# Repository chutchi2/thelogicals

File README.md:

# thelogicals
General file sharing for The Logicals in 2016-2017
This repostiory will contain presentations, Scripts and everything in between. 
Tiffany says its lame
Robert says its baffling

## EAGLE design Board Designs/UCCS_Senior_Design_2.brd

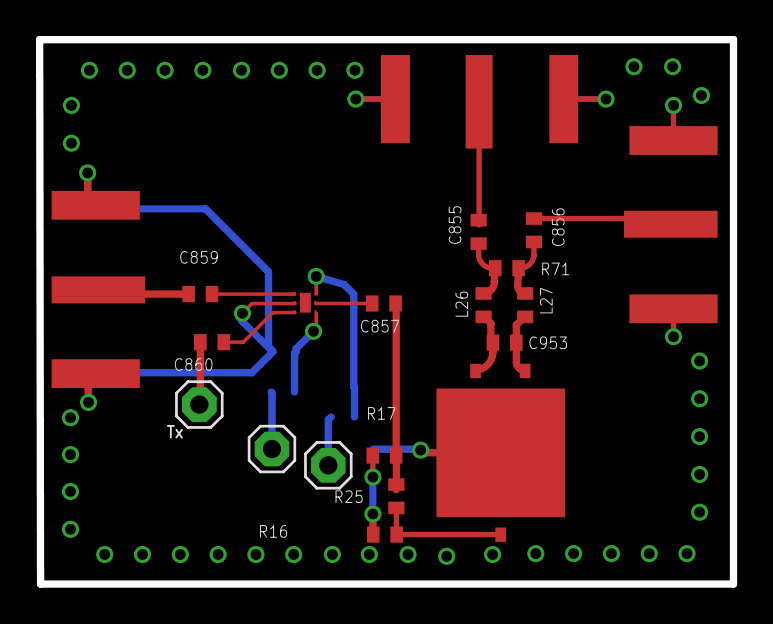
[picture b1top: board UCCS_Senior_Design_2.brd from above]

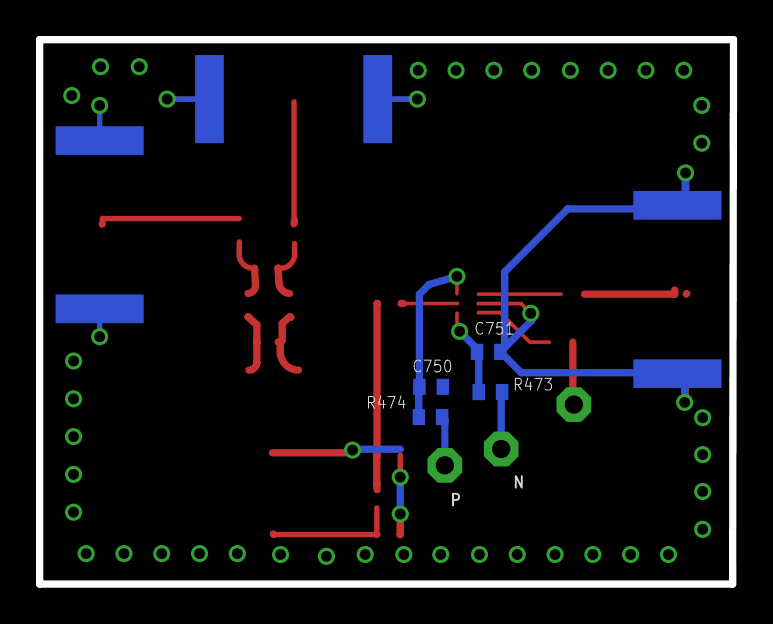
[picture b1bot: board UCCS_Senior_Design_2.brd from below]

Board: 2 copper layers, 38.5 x 30.2 mm, 24 parts (4 on the bottom side), 15 nets.

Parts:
C750, C751, C855, C856, C857, C859, C860: 100 pF; C0402
C953: 400 fF; C0402
E$2: SKY13431-374LF
E$3, E$4, E$5: SMA132289
E$6: BALH-0006SMG
L26, L27: 1 nH; R0402
R16, R17: 221 Ohm; R0402
R25: 23.7 Ohm; R0402
R71: 93.7 Ohm; R0402
R473, R474: 100 Ohm; R0402
RX1_N1, RX1_N2, RX1_P1: 1X01

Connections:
GND: C751.2, E$3.GND, E$3.P$5, E$4.GND, E$4.P$1, E$4.P$2, E$4.P$5, E$5.GND, E$5.P$1, E$5.P$2, E$5.P$5, E$6.GND, R16.2, R17.2
S$1: C751.1, R473.2
S$2: C750.1, R474.2
S$5: C855.2, E$5.P$3
S$6: R473.1, RX1_N1.1
S$10: R16.1, R25.2
S$24: C953.2, L26.1
S$32: C860.2, RX1_P1.1
S$37: R474.1, RX1_N2.1
S$38: C856.2, E$4.P$3
S$40: C953.1, L27.1
S$43: C855.1, L26.2, R71.1
S$44: C856.1, L27.2, R71.2
S$79: C859.2, E$3.P$3
S$85: C857.1, R17.1, R25.1

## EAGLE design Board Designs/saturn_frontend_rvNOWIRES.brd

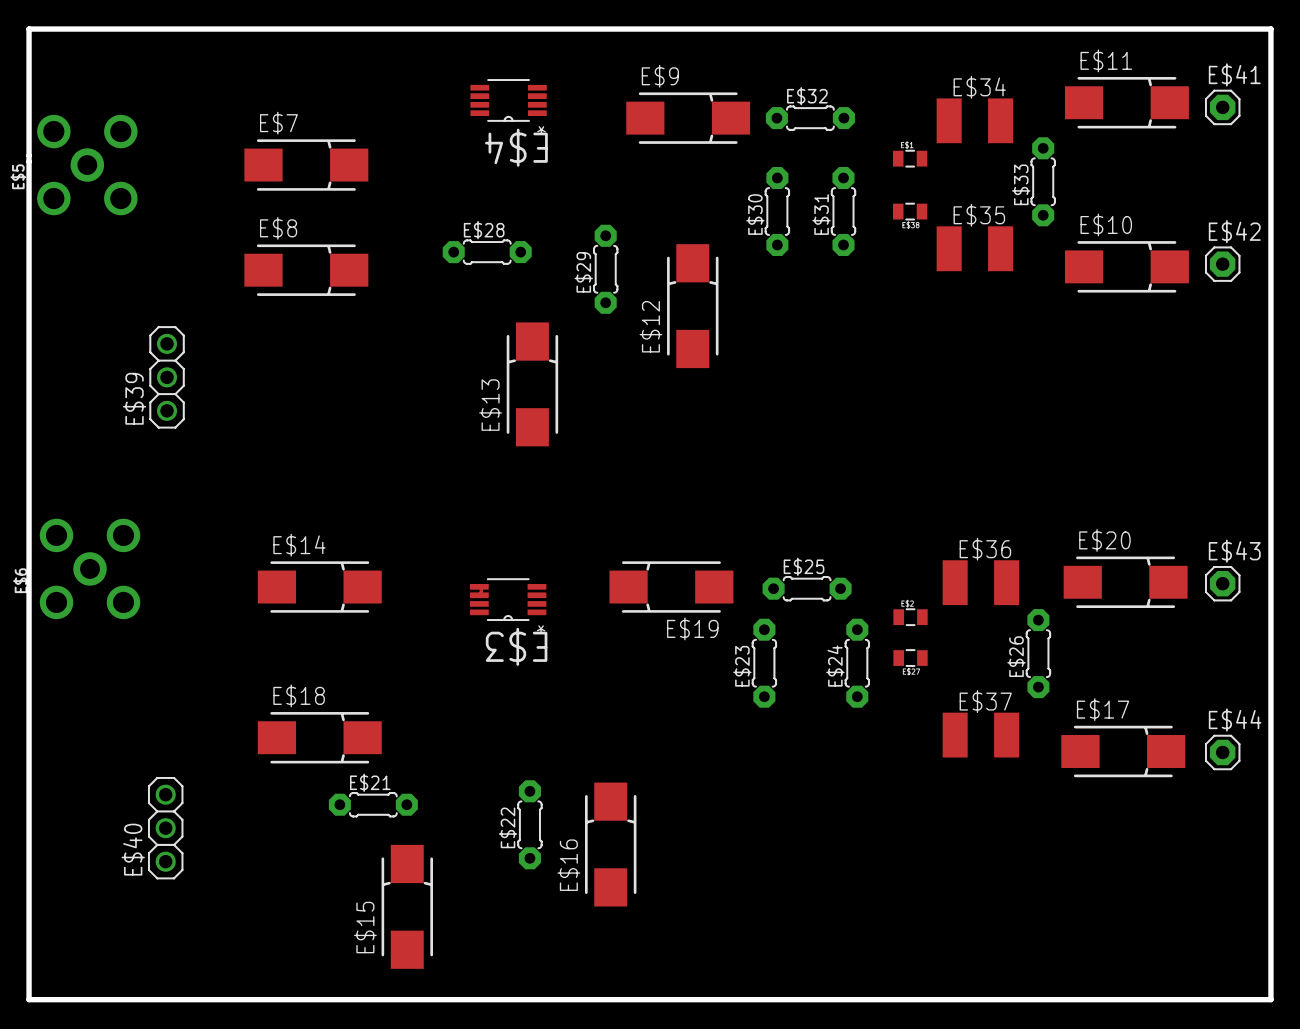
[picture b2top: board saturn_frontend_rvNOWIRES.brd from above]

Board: 2 copper layers, 94.2 x 73.6 mm, 44 parts (0 on the bottom side), 35 nets.

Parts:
E$1, E$2, E$27, E$38: 0805
E$3, E$4: SOP65P490X110-8N
E$5, E$6: SMA90_DIP
E$7, E$8, E$9, E$10, E$11, E$12, E$13, E$14, E$15, E$16, E$17, E$18, E$19, E$20: 100 pF; 085CS_1AR
E$21, E$22, E$28, E$29: 100 Ohm; 0204/5
E$23, E$24, E$30, E$31: 221 Ohm; 0204/5
E$25, E$32: 23.7 Ohm; 0204/5
E$26, E$33: 93.7 Ohm; 0204/5
E$34, E$35, E$36, E$37: 1.0 nH; L1812
E$39, E$40: 1X03
E$41, E$42, E$43, E$44: 1X01

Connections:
S$1: E$11.+, E$41.1
S$5: E$5.ANTENNA, E$7.-
S$6: E$10.-, E$33.1, E$35.2
S$7: E$8.-, E$39.3
S$8: E$28.1, E$39.2
S$10: E$2.1, E$24.2, E$25.2
S$11: E$10.+, E$42.1
S$12: E$11.-, E$33.2, E$34.2
S$14: E$2.2, E$36.1
S$16: E$4.5, E$7.+
S$17: E$20.+, E$43.1
S$18: E$4.8, E$8.+
S$21: E$17.+, E$44.1
S$22: E$4.1, E$28.2
S$23: E$4.2, E$29.2
S$25: E$29.1, E$39.1
S$26: E$9.+, E$30.2, E$32.1
S$27: E$1.1, E$31.2, E$32.2
S$28: E$1.2, E$34.1
S$29: E$35.1, E$38.1
S$32: E$18.-, E$40.3
S$33: E$21.1, E$40.2
S$34: E$22.1, E$40.1
S$36: E$6.ANTENNA, E$14.-
S$37: E$4.3, E$9.-
S$38: E$3.8, E$18.+
S$39: E$3.3, E$19.+
S$40: E$3.1, E$15.+, E$21.2
S$41: E$3.2, E$16.+, E$22.2
S$42: E$19.-, E$23.2, E$25.1
S$43: E$27.1, E$37.1
S$44: E$20.-, E$26.2, E$36.2
S$45: E$17.-, E$26.1, E$37.2
S$46: E$3.5, E$3.6, E$3.7, E$6.GND1, E$6.GND2, E$6.GND3, E$6.GND4, E$14.+, E$15.-, E$16.-, E$23.1, E$24.1, E$27.2
S$47: E$4.6, E$4.7, E$5.GND1, E$5.GND2, E$5.GND3, E$5.GND4, E$12.-, E$13.-, E$30.1, E$31.1, E$38.2

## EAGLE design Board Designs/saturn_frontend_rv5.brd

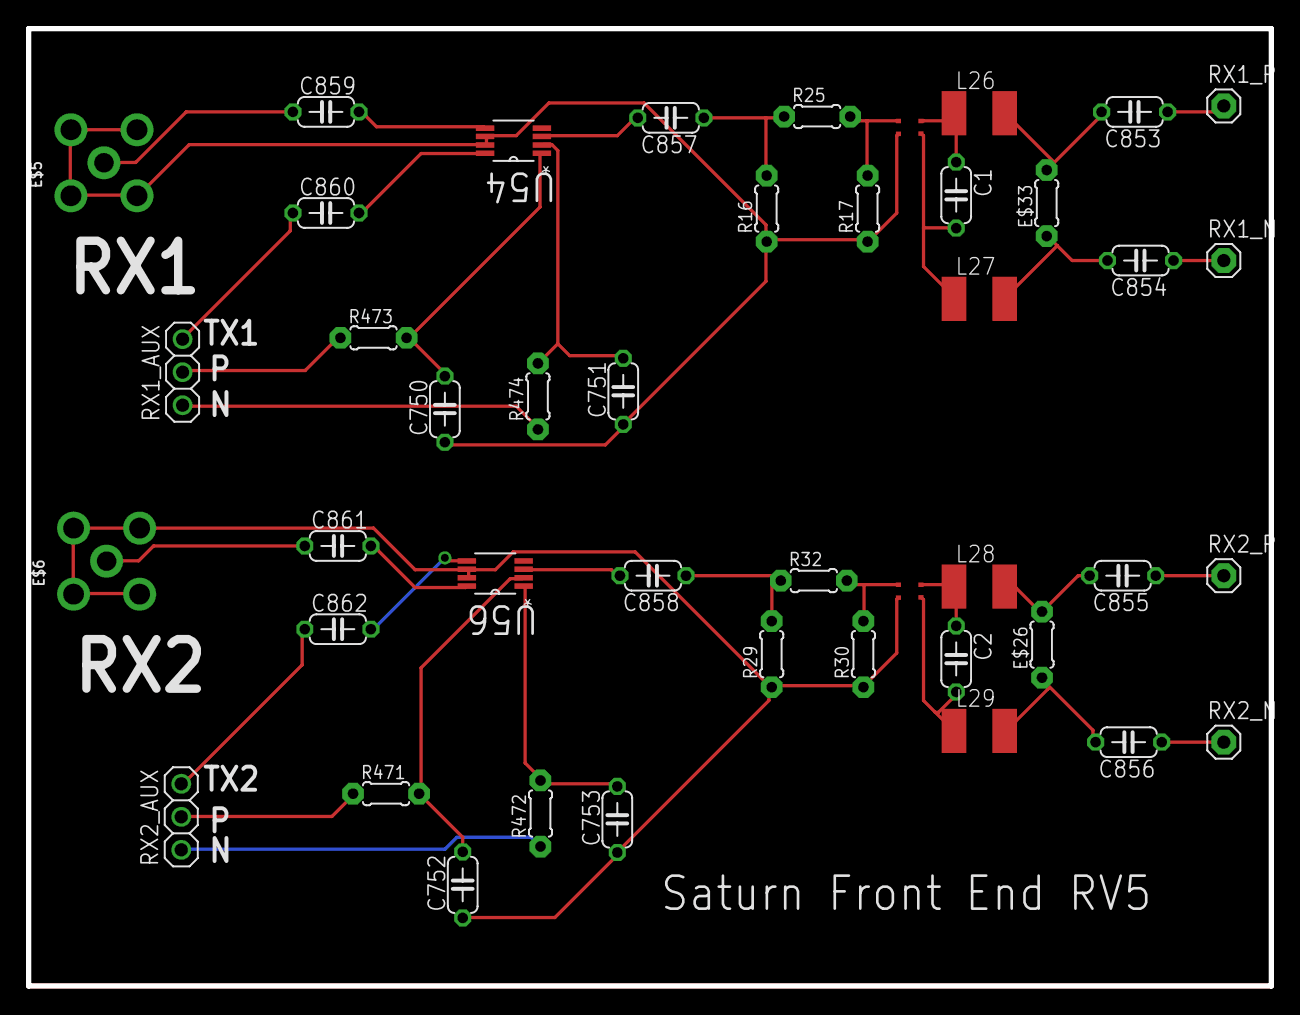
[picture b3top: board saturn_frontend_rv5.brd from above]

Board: 2 copper layers, 95.6 x 73.6 mm, 44 parts (0 on the bottom side), 36 nets.

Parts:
C1, C2: 400 fF; C050-024X044
C750, C751, C752, C753, C853, C854, C855, C856, C857, C858, C859, C860, C861: 100 pF; C050-024X044
C862: C050-024X044
E$1, E$2: BALUN_LOGICALS
E$5, E$6: SMA90_DIP
E$26, E$33: 93.7 Ohm; 0204/5
L26, L27, L28, L29: 1.0 nH; L1812
R16, R17, R29, R30: 221 Ohm; 0204/5
R25, R32: 23.7 Ohm; 0204/5
R471, R472, R473, R474: 100 Ohm; 0204/5
RX1_AUX, RX2_AUX: 1X03
RX1_N, RX1_P, RX2_N, RX2_P: 1X01
U54, U56: SOP65P490X110-8N

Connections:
S$1: E$2.1, R30.2, R32.2
S$2: C2.1, E$2.4, L28.1
S$3: C858.1, R29.2, R32.1
S$5: C855.2, E$26.2, L28.2
S$6: C855.1, RX2_P.1
S$7: C856.2, E$26.1, L29.2
S$8: C2.2, E$2.3, L29.1
S$10: C857.1, R16.2, R25.1
S$12: E$1.1, R17.2, R25.2
S$14: C1.1, E$1.4, L26.1
S$16: C1.2, E$1.3, L27.1
S$18: C853.2, E$33.2, L26.2
S$19: C854.2, E$33.1, L27.2
S$23: C853.1, RX1_P.1
S$24: C854.1, RX1_N.1
S$25: R473.1, RX1_AUX.2
S$27: C750.2, R473.2, U54.1
S$28: C751.2, R474.2, U54.2
S$29: R474.1, RX1_AUX.1
S$32: R471.1, RX2_AUX.2
S$33: C752.2, R471.2, U56.2
S$34: C753.2, R472.2, U56.1
S$35: C861.1, E$6.ANTENNA
S$36: C862.1, RX2_AUX.3
S$37: C860.1, RX1_AUX.3
S$38: C859.1, E$5.ANTENNA
S$39: C859.2, U54.5
S$40: C860.2, U54.8
S$41: C862.2, U56.5
S$42: C861.2, U56.8
S$43: C858.2, U56.3
S$44: C857.2, U54.3
S$45: C750.1, C751.1, E$1.2, E$5.GND1, E$5.GND2, E$5.GND3, E$5.GND4, R16.1, R17.1, U54.6, U54.7
S$46: C752.1, C753.1, E$2.2, E$6.GND1, E$6.GND2, E$6.GND3, E$6.GND4, R29.1, R30.1, U56.6, U56.7
S$47: C856.1, RX2_N.1
S$49: R472.1, RX2_AUX.1

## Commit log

2016-12-27 Tiffany edited the readme
2016-12-27 Robert added readme commentary
2016-12-27 Added Cheat Sheet
2017-01-03 added calibration script
2017-01-04 Added incomplete schematic rv2 of saturn front end
2017-01-05 Most Recent spec doc added
2017-01-05 Added reference schematics from john
2017-01-06 Attempt to add Pspice files
2017-01-06 attempt to add Pspice file
2017-01-06 Reorginized pspice schematic files
2017-01-06 fixed pspice file
2017-01-06 final update of spice files
2017-01-07 added comments to explain cal script
2017-01-07 removed underscores from variables
2017-01-09 Eagle Board RV3 added with updated component names
2017-01-13 complete (?) Pspice - not simulating :,(
2017-01-17 closer to working spice model
2017-01-19 added simple schedule with dates
2017-01-21 simplified spice (v2) with simulation output
2017-01-22 Moved board designs to a seperate directory to keep SPICE/ clean
2017-01-31 spice simulations, output data, and 80% of white paper
2017-02-01 Quick Commit of winSPC python script--unfinished
2017-02-01 Works Better with updated python script
2017-02-02 Updated script to working revision
2017-02-02 FInished tool ready for RTLgic
2017-02-04 Hoping i didn't break the repository
2017-02-06 Added both BOMs
2017-02-06 Added Current Front End Modeled
2017-02-07 Quick library update
2017-02-08 Both Boards mocked up, both need testing
2017-02-08 Fixed the component size in library and in layout
2017-02-08 Added symbols to library
2017-02-09 Very rough scpi conversion
2017-02-09 Fixed boards with Bogdan's comments
2017-02-09 Couple more scpi commands added
2017-02-09 added some scpi commands
2017-02-09 New scpi commands
2017-02-09 More scpi changes
2017-02-09 added different print commands
2017-02-13 Another Revision of the boards, with more sma connectors
2017-02-17 Next Revision of board
2017-02-21 Design Review Presentation Version 1
2017-02-23 Newest Presentation 2_23_2017
2017-02-23 Upteenth Revision of Layout
2017-02-23 cal files added
2017-02-26 Added math script to look at each file
2017-03-03 Updated script ready for test
2017-03-03 Updated power level script
